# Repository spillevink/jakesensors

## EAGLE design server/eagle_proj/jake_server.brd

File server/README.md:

# Jakesensors server

## Todo

- http://blog.blackoise.de/2016/02/fixing-your-cheap-nrf24l01-palna-module/
- https://github.com/patrick--/AVR-ENC28J60-Examples
- http://electronics.stackexchange.com/questions/57998/can-i-use-icsp-if-components-share-mosi-sck-pins

## Parts

| 2 | 1206 100uf          | https://goo.gl/RsohKt | + 4.1         |
| 1 | ams1117-3.3         | https://goo.gl/9Ziazm | + 2           |
| 1 | 2 row smt           | https://goo.gl/3X4GVC | + 6.68        |
| 1 | 2x6 female 90 angle | https://goo.gl/FL6Iek | + 13.5        |
| 6 | 1206 LED white      | https://goo.gl/6jloJx | + 1.31        |
| 1 | ENC28J60 robotdyn   | https://goo.gl/FGyIcW | + 3.98+3.98   |
| 2 | 0402 10k ohm        | https://goo.gl/V3T4Ai | + 0.25        |
| 1 | nrf24L01+PA+LNA     | https://goo.gl/pA05G6 | + 2.49 + 4.29 |
| 1 | 6x.3.5mm smd switch | https://goo.gl/42e7Um | + 6.86        |
| 1 | atmega328p-mu       | https://goo.gl/3dVVzl | + 11          |
| 1 | usb type c breakout | https://goo.gl/ijW7pn | + 1.85+1.85   |

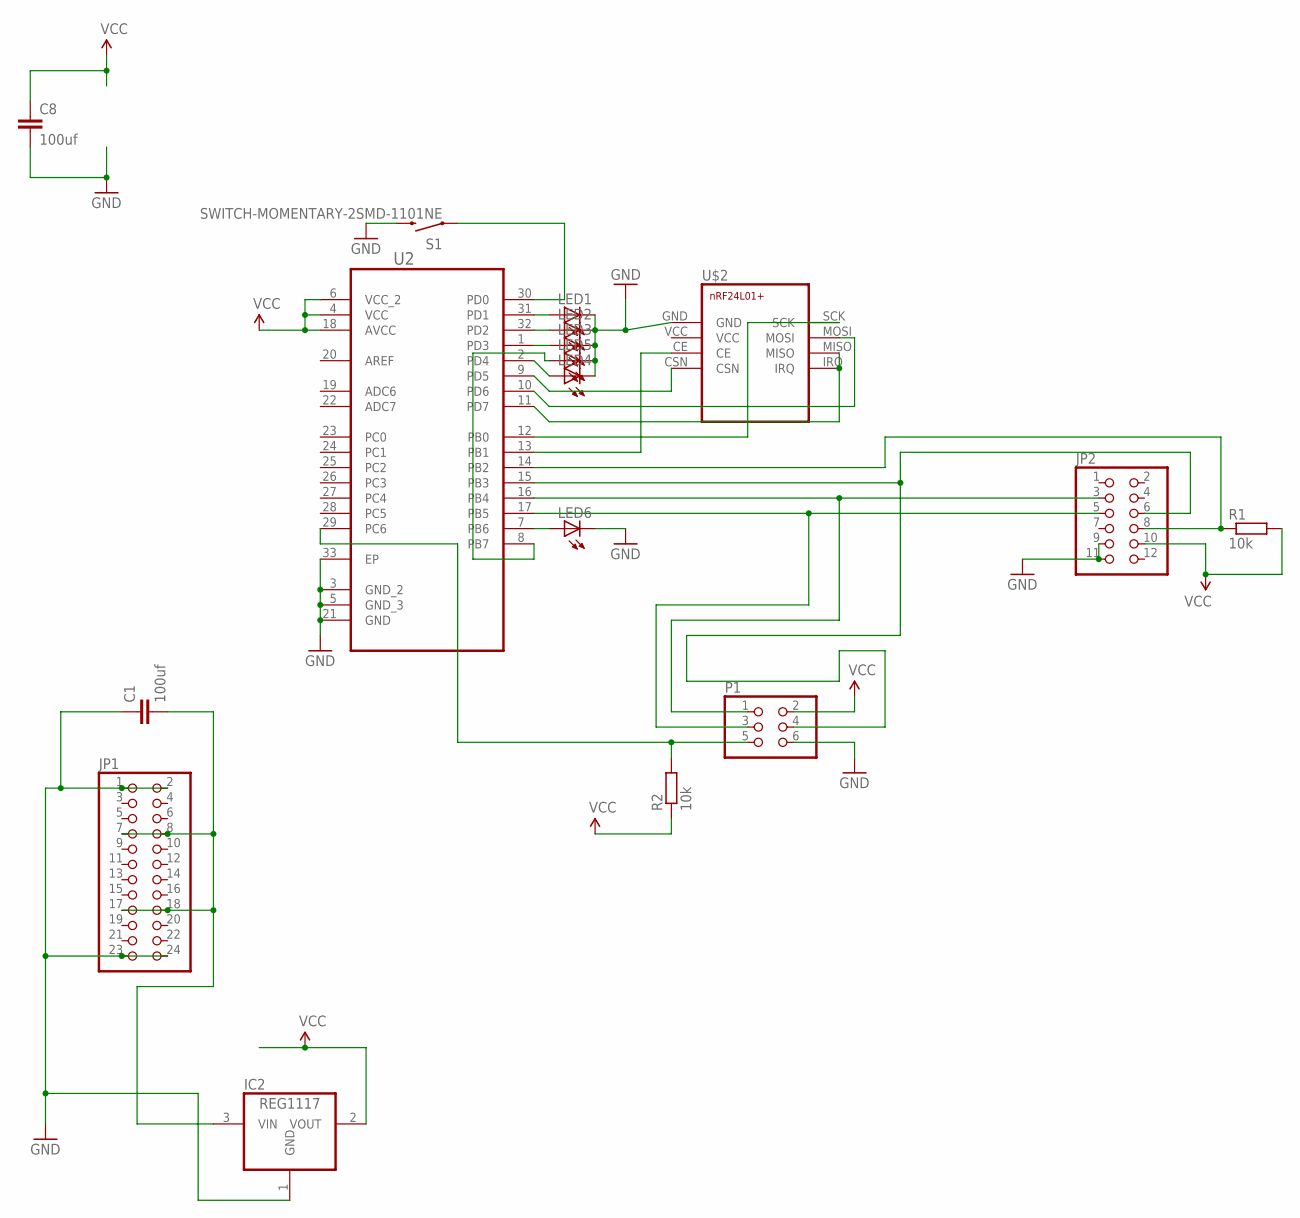
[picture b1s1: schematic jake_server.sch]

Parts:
C1, C8: 100uf; 1206
IC2: REG1117; SOT223
JP1: PINHD-2X12SMT; 2X12_SMT
JP2: PINHD-2X6/90; 2X06/90
LED1, LED2, LED3, LED4, LED5, LED6: LED1206; LED-1206
P1: PINHD-2X3SMT; 2X03_SMT
R1, R2: 10k; R0402
S1: SWITCH-MOMENTARY-2SMD-1101NE; TACTILE-SWITCH-1101NE
U2: ATMEGA328P-MU; QFN50P500X500X100-33N
U$2: NRF24L01+

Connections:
GND: C1.1, C8.2, IC2.1 (GND), JP1.1, JP1.2, JP1.23, JP1.24, JP2.9, JP2.11, LED1.C, LED2.C, LED3.C, LED4.C, LED5.C, LED6.C, P1.6, S1.2, U2.3 (GND_2), U2.5 (GND_3), U2.21 (GND), U2.33 (EP), U$2.GND
unnamed: C1.2, IC2.3 (VIN), JP1.7, JP1.8, JP1.17, JP1.18
unnamed: U2.13 (PB1), U$2.CE
unnamed: U2.12 (PB0), U$2.SCK
unnamed: U2.11 (PD7), U$2.IRQ, U$2.MISO
unnamed: U2.10 (PD6), U$2.MOSI
unnamed: U2.9 (PD5), U$2.CSN
unnamed: LED5.A, U2.8 (PB7)
unnamed: JP2.5, P1.3, U2.17 (PB5)
unnamed: JP2.6, P1.4, U2.15 (PB3)
unnamed: JP2.3, P1.1, U2.16 (PB4)
unnamed: P1.5, R2.2, U2.29 (PC6)
unnamed: LED6.A, U2.7 (PB6)
unnamed: LED4.A, U2.2 (PD4)
unnamed: LED3.A, U2.1 (PD3)
unnamed: LED2.A, U2.32 (PD2)
unnamed: LED1.A, U2.31 (PD1)
unnamed: S1.1, U2.30 (PD0)
unnamed: JP2.8, R1.1, U2.14 (PB2)
VCC: C8.1, IC2.2 (VOUT), JP2.10, P1.2, R1.2, R2.1, U2.4 (VCC), U2.6 (VCC_2), U2.18 (AVCC), U$2.VCC

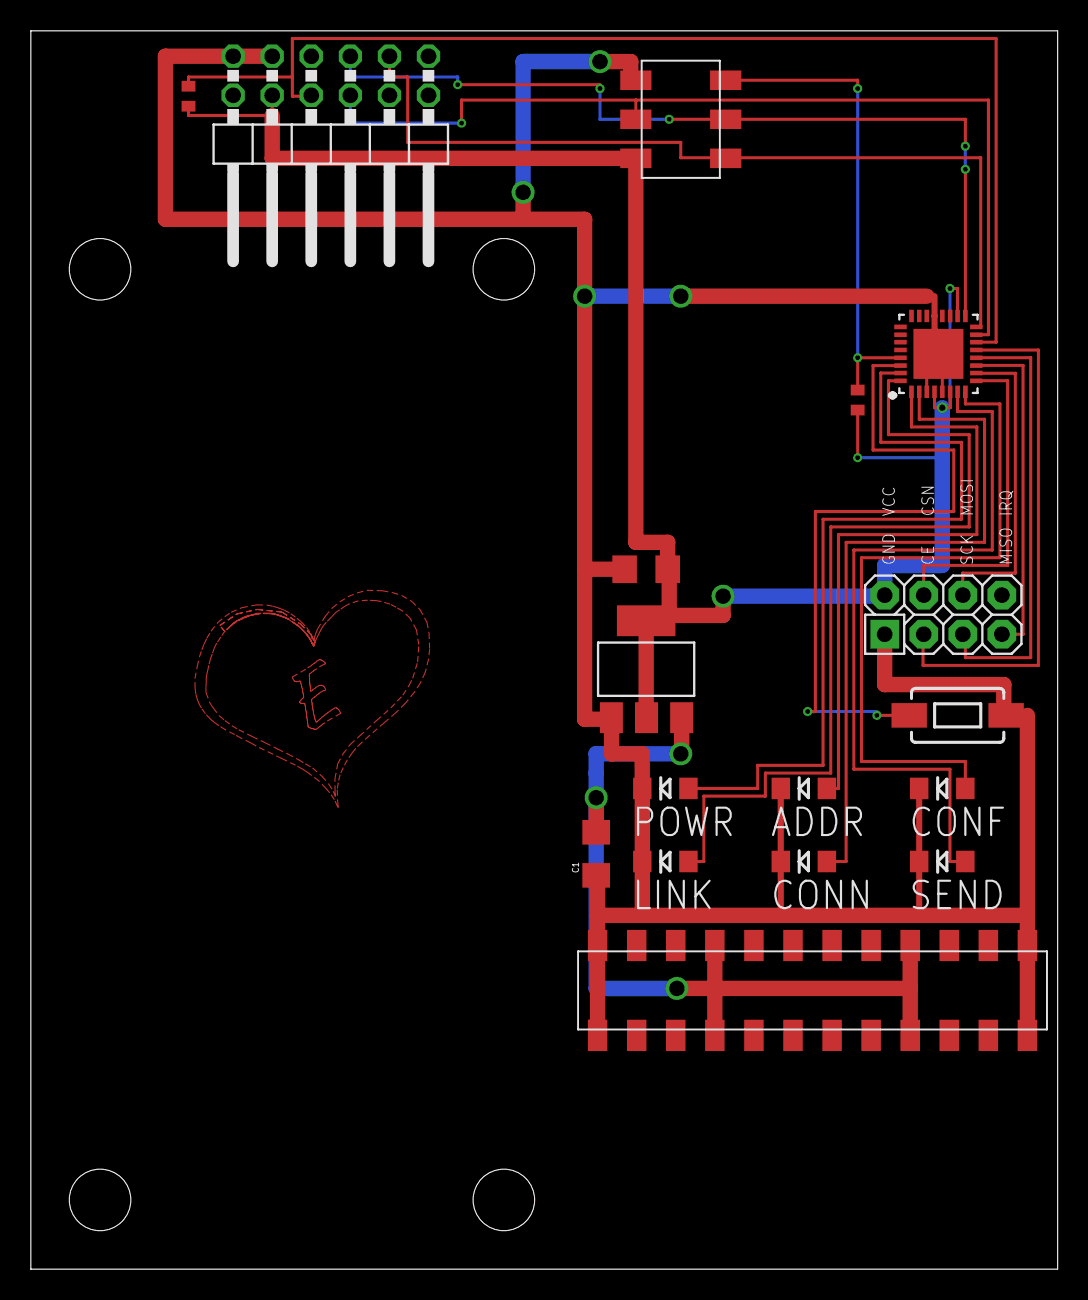
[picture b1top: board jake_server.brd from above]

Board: 2 copper layers, 66.8 x 80.5 mm, 17 parts (0 on the bottom side), 20 nets.

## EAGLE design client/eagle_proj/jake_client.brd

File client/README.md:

# Todo

# Components

| Schematic | Name                | Qty  |   Price | Min order | URL                   |
| --------- | ------------------- | ----:| -------:| --------- | --------------------- |
| C8        | 1206 CAP 100uf      |    1 |  $0.041 |     $4.10 | https://goo.gl/bVkBAX |
| IC1       | BME280              |    1 |   $3.60 |    $17.00 | https://goo.gl/V5KRjY |
| JP1       | 1X3 pin header      |    1 | $0.0228 |     $2.28 | https://goo.gl/KC9M8a |
| LED1      | 0402 LED White      |    1 | $0.0512 |     $5.12 | https://goo.gl/aWK7NA |
| P1        | 2x3 pin header      |    1 | $0.0352 |     $3.52 | https://goo.gl/UTnZWO |
| R1        | 0402 RES 10k        |    1 | $0.0024 |     $0.24 | https://goo.gl/MR4Lh3 |
| R3        | 0402 RES 39         |    1 | $0.0024 |     $0.24 | https://goo.gl/Ukcpla |
| S1        | 6x3.5mm switch      |    1 | $0.0686 |     $6.86 | https://goo.gl/Hy7T2Z |
| U1        | NRF24L01+ smd       |    1 |  $0.320 |     $3.20 | https://goo.gl/Wg053p |
| U2        | ATMEGA328P-MU (QFN) |    1 |  $1.045 |    $10.45 | https://goo.gl/zReri2 |
| U3        | APDS-9930           |    1 |   $1.10 |    $11.00 | https://goo.gl/BRHXgw |
| U4        | RPI-1031            |    1 |   $0.90 |    $18.00 | https://goo.gl/n29J7n |
| V1        | CR123A holder       |    1 |  $0.395 |     $7.90 | https://goo.gl/09fL5B |

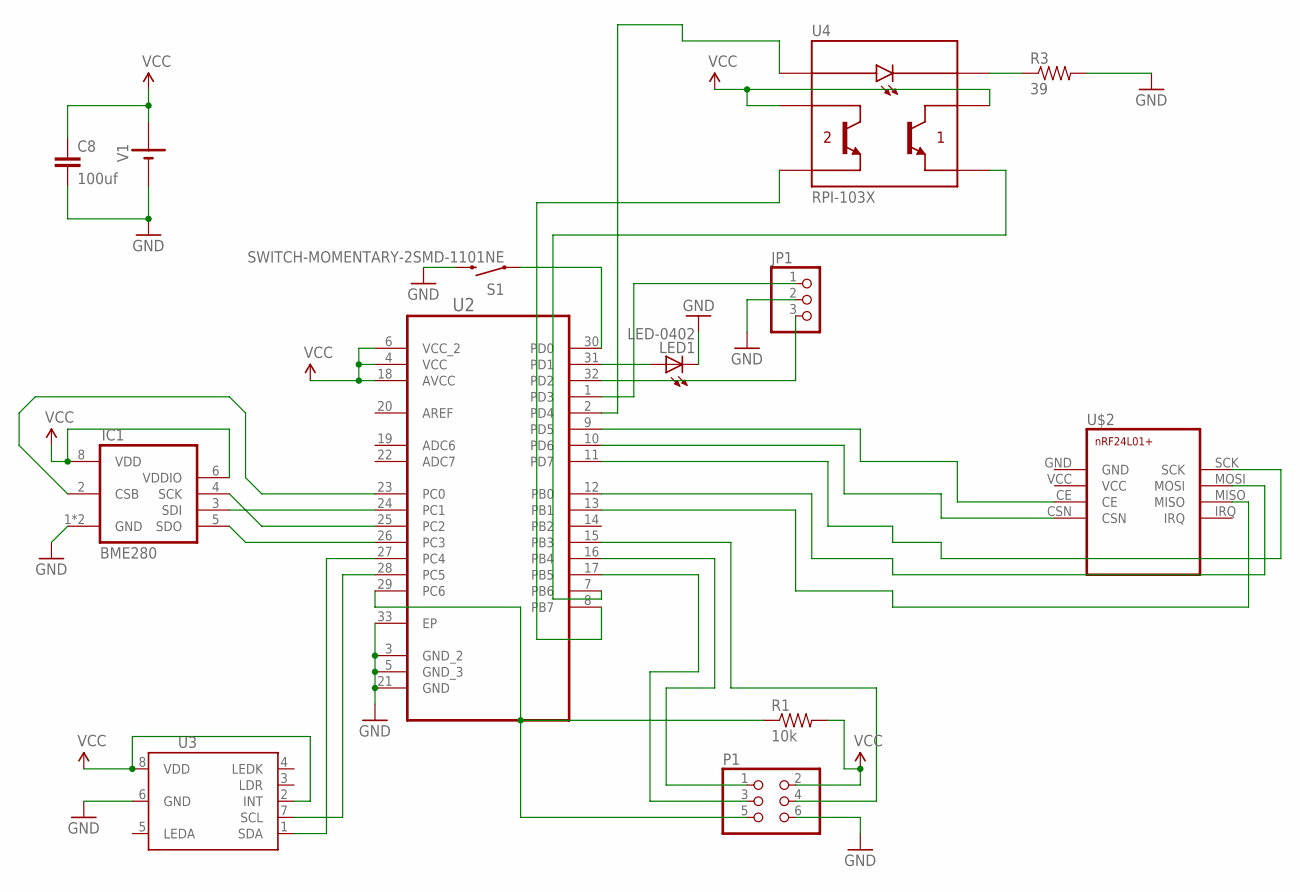
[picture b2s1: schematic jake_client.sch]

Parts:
C8: 100uf; 1206
IC1: BME280
JP1: PINHD-1X31X03_SMT; 1X03_SMT
LED1: LED-0402; 0402-LED
P1: PINHD-2X3SMT; 2X03_SMT
R1: 10k; 0402-RES
R3: 39; 0402-RES
S1: SWITCH-MOMENTARY-2SMD-1101NE; TACTILE-SWITCH-1101NE
U2: ATMEGA328P-MU; QFN50P500X500X100-33N
U3: APDS-9960
U4: RPI-103X
U$2: NRF24L01+NRF24L01+MINI; NRF24L01+MINI
V1: TAKACHI_BATT-CR123A; TAKACHI_CR123A

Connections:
GND: C8.2, IC1.1 (GND), IC1.7 (GND), JP1.2, LED1.C, P1.6, R3.2, S1.2, U2.3 (GND_2), U2.5 (GND_3), U2.21 (GND), U2.33 (EP), U3.6 (GND), U$2.GND, V1.-
unnamed: U2.12 (PB0), U$2.MOSI
unnamed: LED1.A, U2.31 (PD1)
unnamed: IC1.3 (SDI), U2.24 (PC1)
unnamed: IC1.5 (SDO), U2.26 (PC3)
unnamed: P1.3, U2.17 (PB5)
unnamed: P1.4, U2.15 (PB3)
unnamed: P1.1, U2.16 (PB4)
unnamed: P1.5, R1.1, U2.29 (PC6)
unnamed: U2.27 (PC4), U3.1 (SDA)
unnamed: U2.28 (PC5), U3.7 (SCL)
unnamed: IC1.4 (SCK), U2.25 (PC2)
unnamed: U2.9 (PD5), U$2.CE
unnamed: U2.10 (PD6), U$2.CSN
unnamed: U2.11 (PD7), U$2.SCK
unnamed: IC1.2 (CSB), U2.23 (PC0)
unnamed: JP1.3, U2.32 (PD2)
unnamed: JP1.1, U2.1 (PD3)
unnamed: S1.1, U2.30 (PD0)
unnamed: U2.2 (PD4), U4.6 (ANODE)
unnamed: U2.7 (PB6), U4.1 (E1)
unnamed: U2.8 (PB7), U4.4 (E2)
unnamed: R3.1, U4.3 (CATHODE)
unnamed: U2.13 (PB1), U$2.MISO
VCC: C8.1, IC1.6 (VDDIO), IC1.8 (VDD), P1.2, R1.2, U2.4 (VCC), U2.6 (VCC_2), U2.18 (AVCC), U3.2 (INT), U3.8 (VDD), U4.2 (C1), U4.5 (C2), U$2.VCC, V1.+

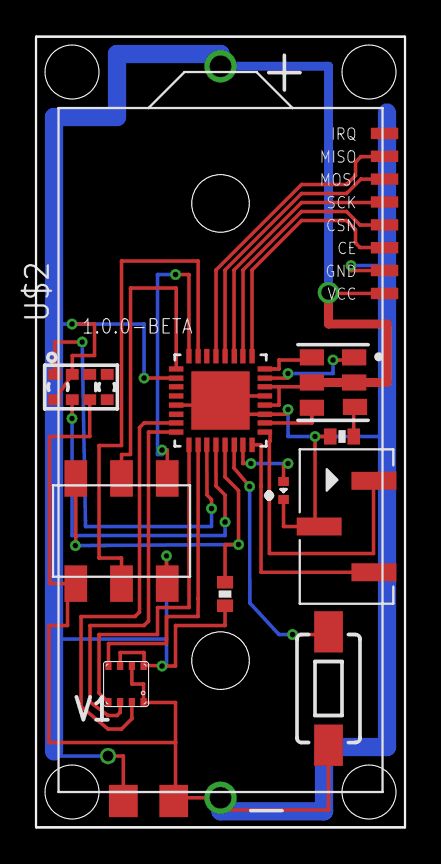
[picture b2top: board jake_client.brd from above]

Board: 2 copper layers, 20.5 x 44.0 mm, 13 parts (0 on the bottom side), 25 nets.

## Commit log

2016-11-13 initial
2016-11-14 Update bill of materials
2016-11-15 start of server
2016-11-16 Server updates
2016-11-16 gitignore
2016-11-16 Cleanup
2016-11-16 Eagle files rename
2016-11-16 Clared client todo
2016-11-16 Fix voltage regulator
2016-11-16 server bill of materials

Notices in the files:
parts and their libraries:
SparkFun-Capacitors: Licensing: Creative Commons ShareAlike 4.0 International - https://creativecommons.org/licenses/by-sa/4.0
